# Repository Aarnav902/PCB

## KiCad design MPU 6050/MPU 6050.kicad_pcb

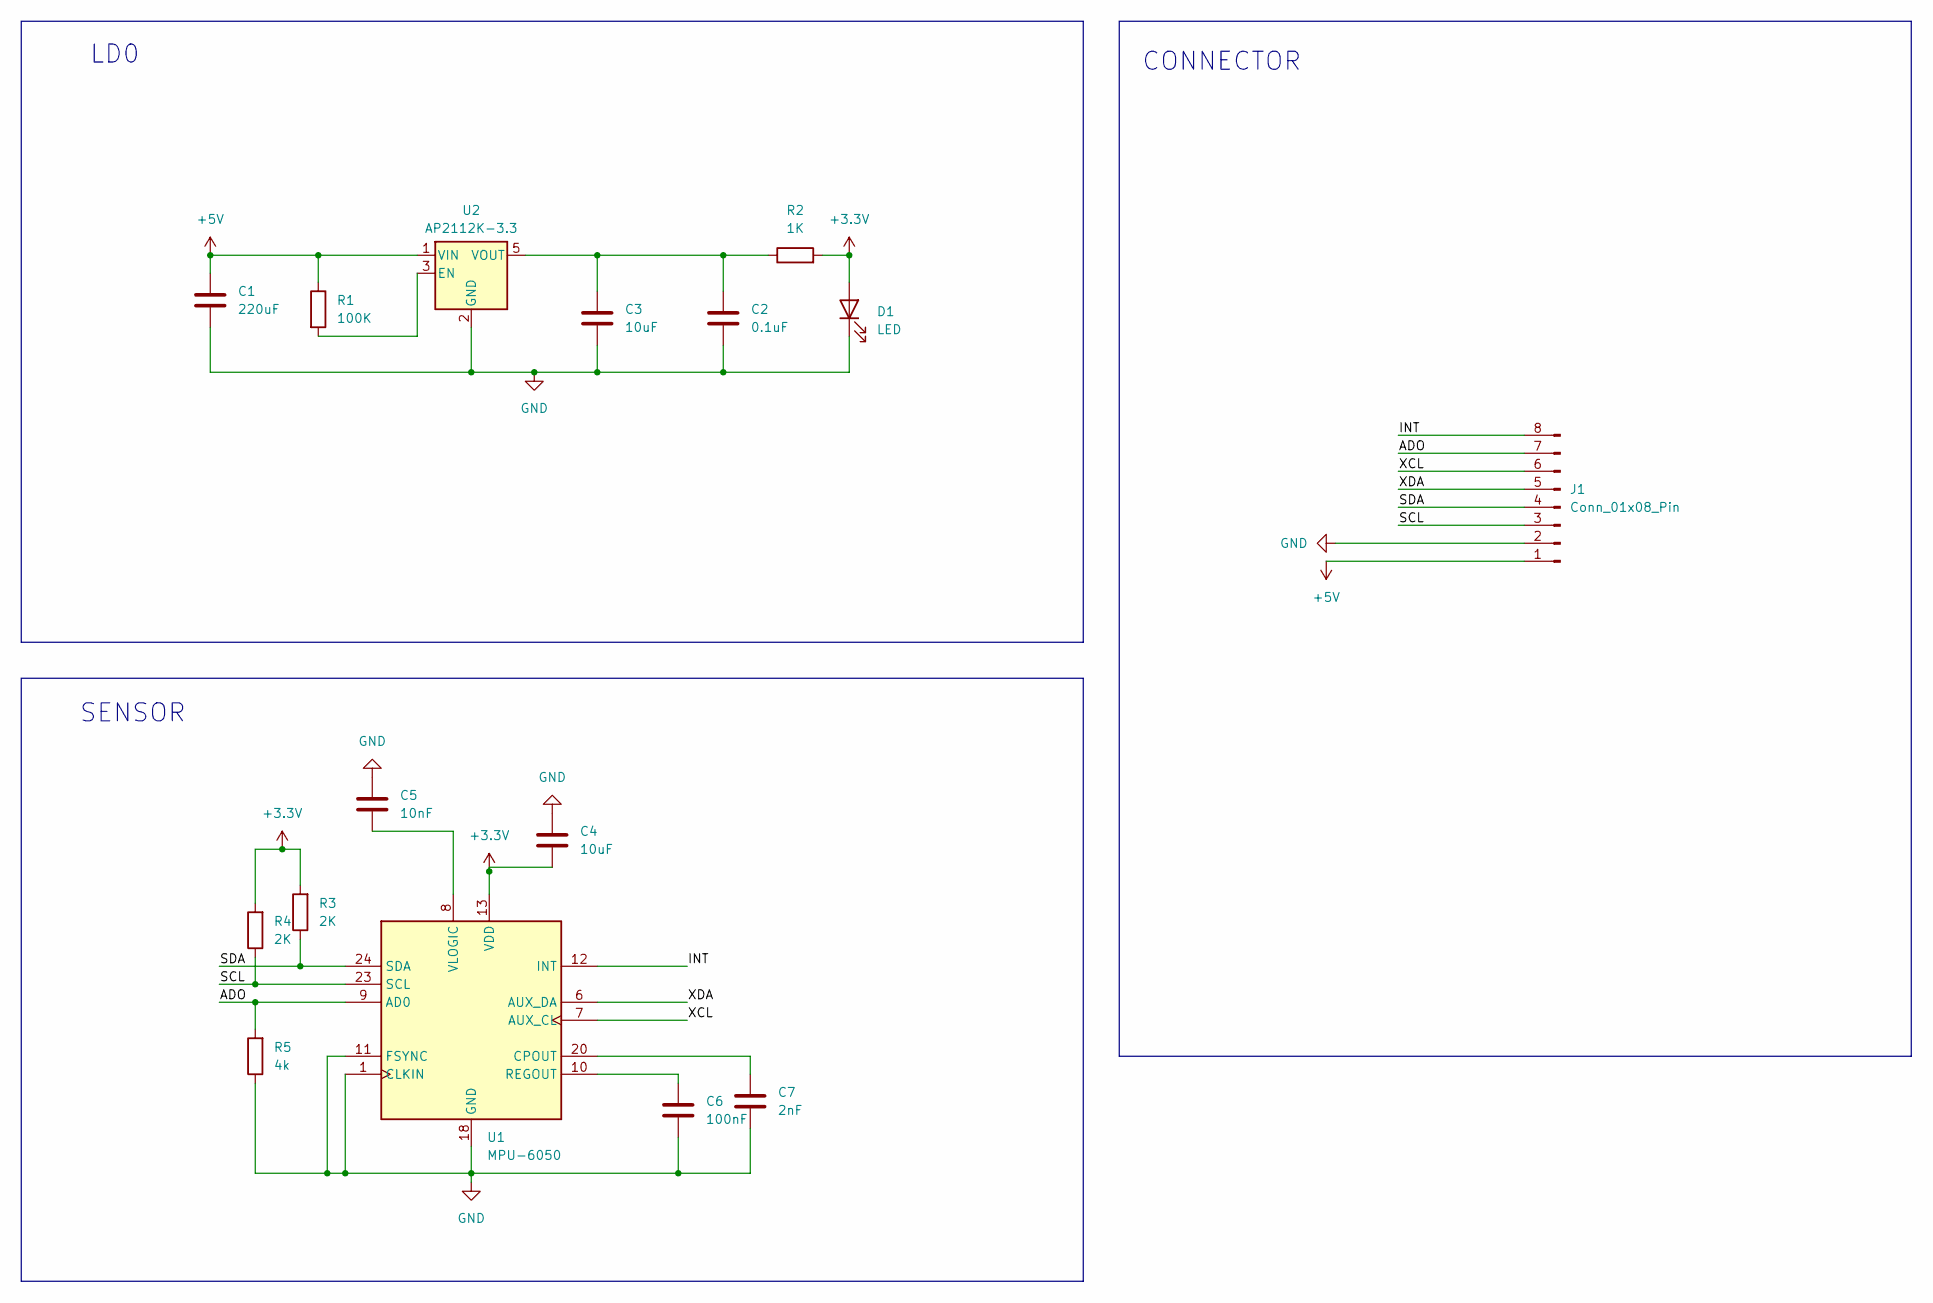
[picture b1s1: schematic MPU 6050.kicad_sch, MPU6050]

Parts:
C1: 220uF; C_0805_2012Metric
C2: 0.1uF; C_0603_1608Metric
C3, C4: 10uF; C_0805_2012Metric
C5: 10nF; C_0603_1608Metric
C6: 100nF; C_0603_1608Metric
C7: 2nF; C_0603_1608Metric
D1: LED; LED_0603_1608Metric
J1: Conn_01x08_Pin; PinHeader_1x08_P2.54mm_Vertical
R1: 100K; R_0603_1608Metric
R2: 1K; R_0603_1608Metric
R3, R4: 2K; R_0603_1608Metric
R5: 4k; R_0603_1608Metric
U1: MPU-6050; InvenSense_QFN-24_4x4mm_P0.5mm
U2: AP2112K-3.3; SOT-23-5

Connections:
+3.3V: C4.2, D1.2 (A), R2.2, R3.2, R4.2, U1.13 (VDD)
+5V: C1.1, J1.1, R1.1, U2.1 (VIN)
/ADO: J1.7, R5.2, U1.9 (AD0)
/INT: J1.8, U1.12 (INT)
/SCL: J1.3, R4.1, U1.23 (SCL)
/SDA: J1.4, R3.1, U1.24 (SDA)
/XCL: J1.6, U1.7 (AUX_CL)
/XDA: J1.5, U1.6 (AUX_DA)
GND: C1.2, C2.2, C3.2, C4.1, C5.1, C6.2, C7.2, D1.1 (K), J1.2, R5.1, U1.1 (CLKIN), U1.11 (FSYNC), U1.18 (GND), U2.2 (GND)
unnamed: C7.1, U1.20 (CPOUT)
unnamed: C6.1, U1.10 (REGOUT)
unnamed: C5.2, U1.8 (VLOGIC)
unnamed: R1.2, U2.3 (EN)
unnamed: C2.1, C3.1, R2.1, U2.5 (VOUT)

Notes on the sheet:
LD0
SENSOR
CONNECTOR

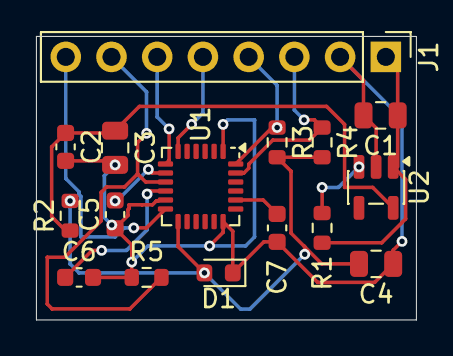
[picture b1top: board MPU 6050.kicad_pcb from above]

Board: 2 copper layers, 21.1 x 15.8 mm, 16 parts (0 on the bottom side), 14 nets.

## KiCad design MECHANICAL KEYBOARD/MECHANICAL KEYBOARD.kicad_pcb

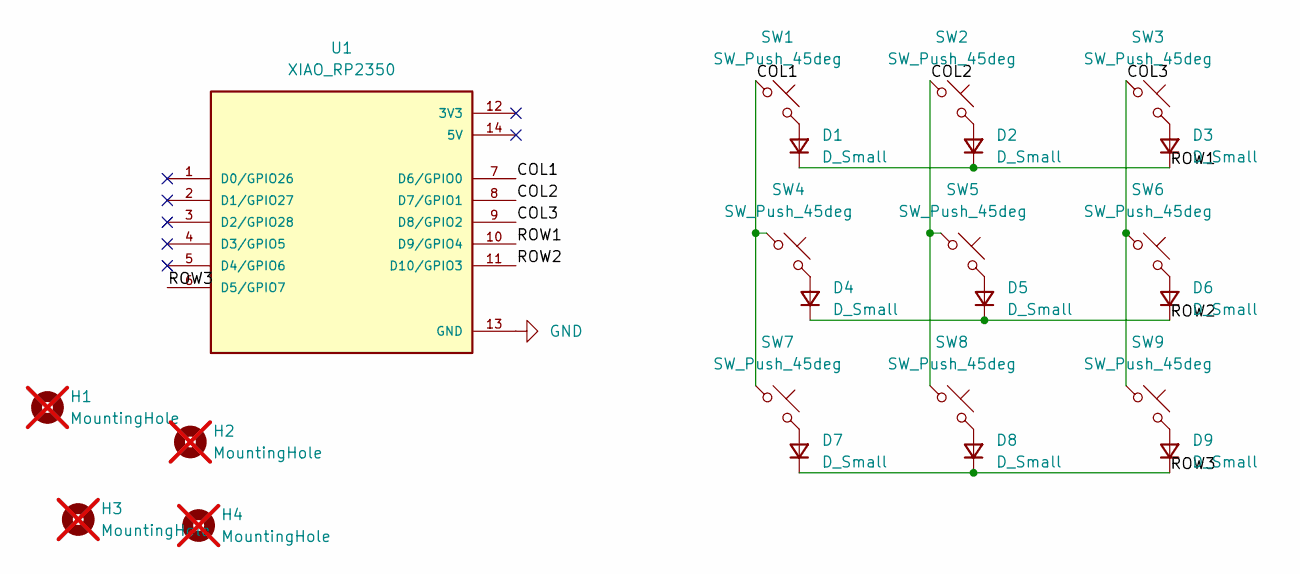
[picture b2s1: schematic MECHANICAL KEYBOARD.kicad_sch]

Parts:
D1, D2, D3, D4, D5, D6, D7, D8, D9: D_Small; D_SOD-123
H1, H2, H3, H4: MountingHole; MountingHole_3.2mm_M3; not fitted
SW1, SW2, SW3, SW4, SW5, SW6, SW7, SW8, SW9: SW_Push_45deg; SW_Cherry_MX_1.00u_PCB
U1: XIAO_RP2350; MODULE_XIAO_RP2350; PARTREV April 18th, 2026

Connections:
/COL1: SW1.1, SW4.1, SW7.1, U1.7 (D6/GPIO0)
/COL2: SW2.1, SW5.1, SW8.1, U1.8 (D7/GPIO1)
/COL3: SW3.1, SW6.1, SW9.1, U1.9 (D8/GPIO2)
/ROW1: D1.1 (K), D2.1 (K), D3.1 (K), U1.10 (D9/GPIO4)
/ROW2: D4.1 (K), D5.1 (K), D6.1 (K), U1.11 (D10/GPIO3)
/ROW3: D7.1 (K), D8.1 (K), D9.1 (K), U1.6 (D5/GPIO7)
GND: U1.13 (GND)
unnamed: D1.2 (A), SW1.2
unnamed: D2.2 (A), SW2.2
unnamed: D3.2 (A), SW3.2
unnamed: D4.2 (A), SW4.2
unnamed: D5.2 (A), SW5.2
unnamed: D6.2 (A), SW6.2
unnamed: D7.2 (A), SW7.2
unnamed: D8.2 (A), SW8.2
unnamed: D9.2 (A), SW9.2

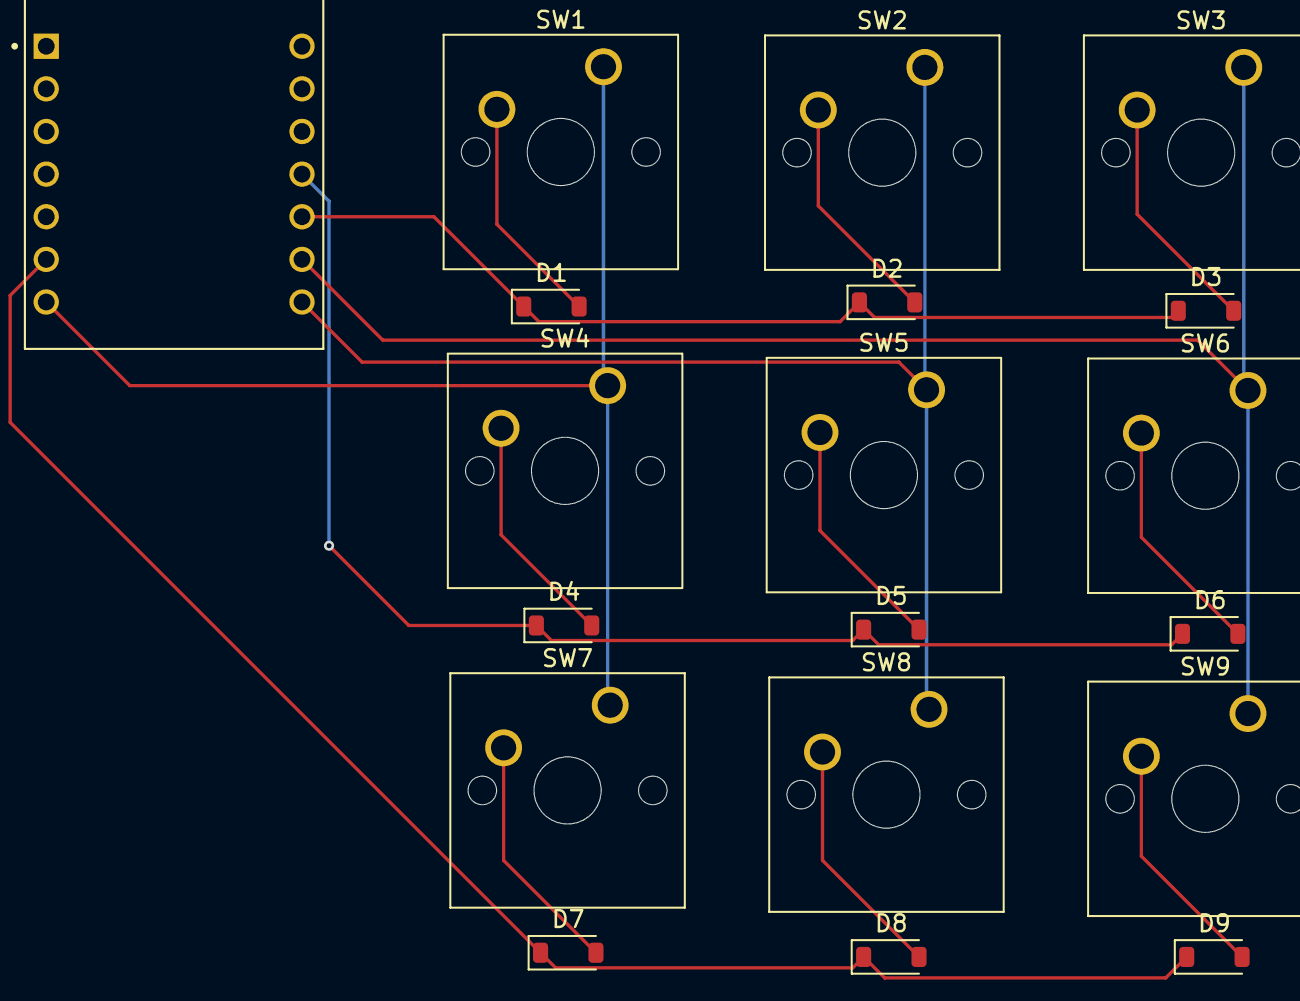
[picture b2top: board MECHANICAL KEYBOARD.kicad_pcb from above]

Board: 2 copper layers, 23 parts (0 on the bottom side), 15 nets.

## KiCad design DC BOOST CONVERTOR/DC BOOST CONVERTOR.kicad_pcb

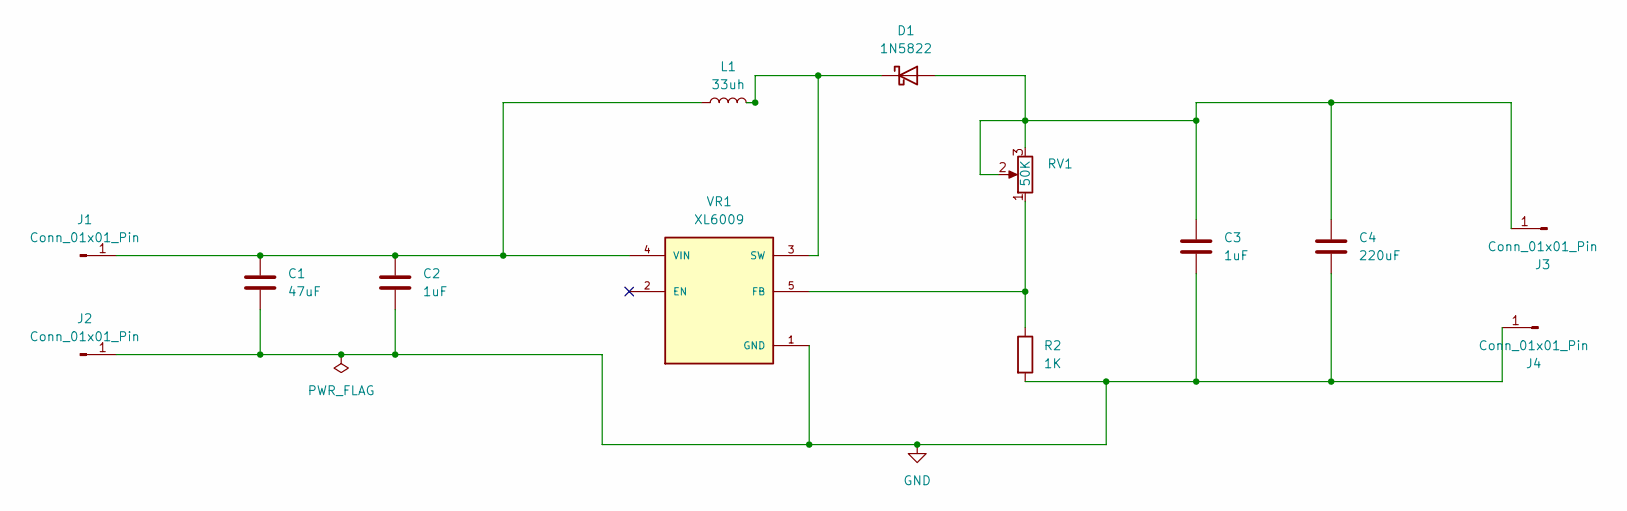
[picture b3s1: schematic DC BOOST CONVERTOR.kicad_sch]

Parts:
C1: 47uF; CP_Radial_D6.3mm_P2.50mm
C2, C3: 1uF; C_0805_2012Metric
C4: 220uF; CP_Radial_D8.0mm_P3.50mm
D1: 1N5822; D_DO-201AD_P15.24mm_Horizontal
J1, J2, J3, J4: Conn_01x01_Pin; Banana_Jack_1Pin
L1: 33uh; L_12x12mm_H8mm
R2: 1K; R_0805_2012Metric
RV1: 50K; Potentiometer_Bourns_3296W_Vertical
VR1: XL6009; DPAK170P1435X465-6N; PARTREV 1.1

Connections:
GND: C1.2, C2.2, C3.2, C4.2, J2.1 (Pin_1_1), J4.1 (Pin_1_1), R2.2, VR1.1 (GND)
unnamed: C3.1, C4.1, D1.2 (A), J3.1 (Pin_1_1), RV1.2, RV1.3
unnamed: D1.1 (K), L1.2, VR1.3 (SW), VR1.6 (SW)
unnamed: C1.1, C2.1, J1.1 (Pin_1_1), L1.1, VR1.4 (VIN)
unnamed: R2.1, RV1.1, VR1.5 (FB)

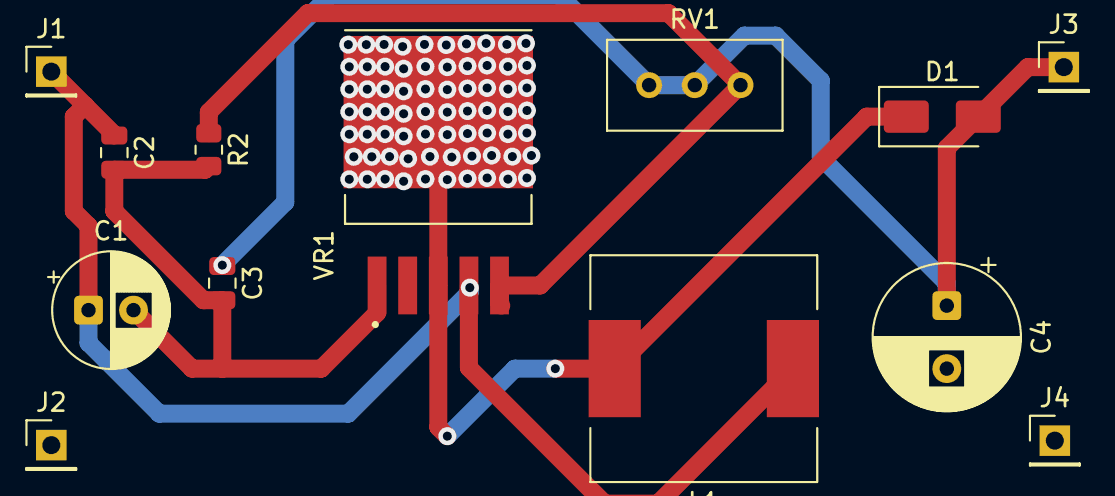
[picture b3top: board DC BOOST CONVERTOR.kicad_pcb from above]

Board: 2 copper layers, 13 parts (0 on the bottom side), 5 nets.

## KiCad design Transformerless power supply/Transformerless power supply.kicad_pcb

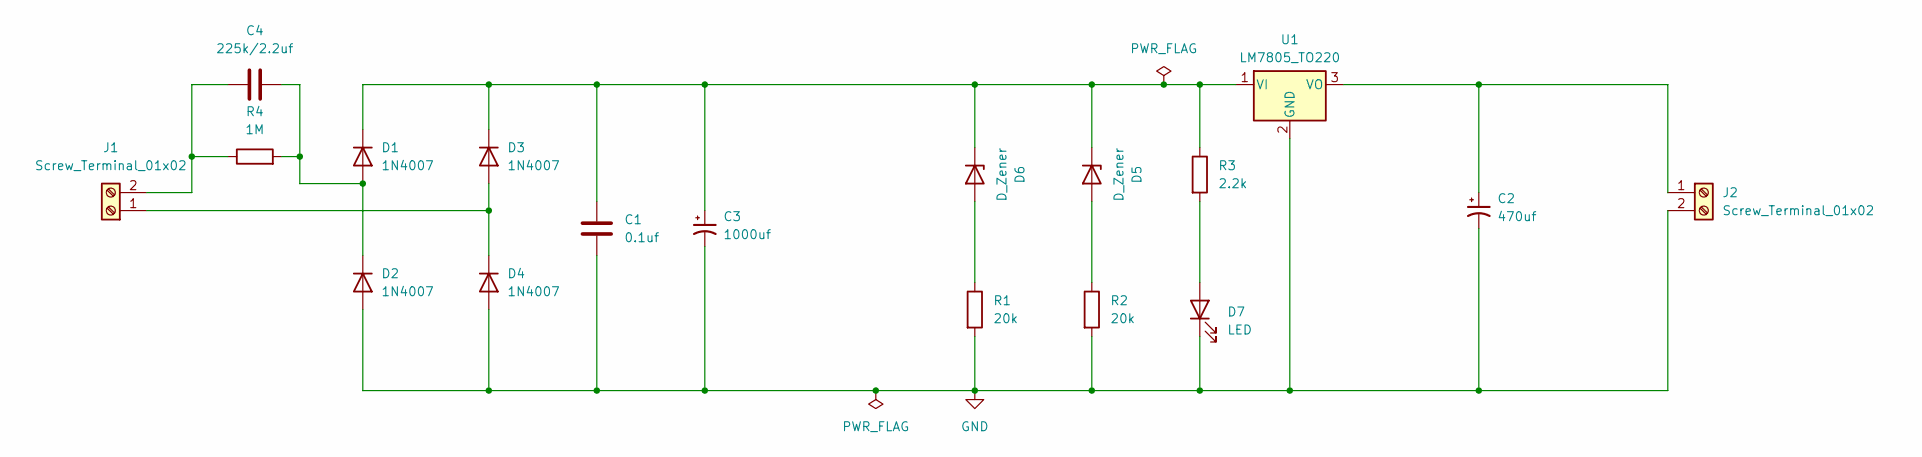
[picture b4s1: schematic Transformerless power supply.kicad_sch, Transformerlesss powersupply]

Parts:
C1: 0.1uf; C_Disc_D4.7mm_W2.5mm_P5.00mm
C2: 470uf; CP_Radial_D10.0mm_P3.80mm
C3: 1000uf; CP_Radial_D10.0mm_P5.00mm
C4: 225k/2.2uf; C_Rect_L18.0mm_W6.0mm_P15.00mm_FKS3_FKP3
D1, D2, D3, D4: 1N4007; D_DO-41_SOD81_P10.16mm_Horizontal
D5, D6: D_Zener; D_A-405_P7.62mm_Horizontal
D7: LED; LED_D5.0mm
J1, J2: Screw_Terminal_01x02; TerminalBlock_MaiXu_MX126-5.0-02P_1x02_P5.00mm
R1, R2: 20k; R_Axial_DIN0207_L6.3mm_D2.5mm_P7.62mm_Horizontal
R3: 2.2k; R_Axial_DIN0207_L6.3mm_D2.5mm_P7.62mm_Horizontal
R4: 1M; R_Axial_DIN0207_L6.3mm_D2.5mm_P7.62mm_Horizontal
U1: LM7805_TO220; TO-220-3_Vertical

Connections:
GND: C1.2, C2.2, C3.2, D2.2 (A), D4.2 (A), D7.1 (K), J2.2, R1.2, R2.2, U1.2 (GND)
unnamed: C4.2, D1.2 (A), D2.1 (K), R4.2
unnamed: C1.1, C3.1, D1.1 (K), D3.1 (K), D5.1 (K), D6.1 (K), R3.1, U1.1 (VI)
unnamed: D3.2 (A), D4.1 (K), J1.1
unnamed: D5.2 (A), R2.1
unnamed: D6.2 (A), R1.1
unnamed: D7.2 (A), R3.2
unnamed: C4.1, J1.2, R4.1
unnamed: C2.1, J2.1, U1.3 (VO)

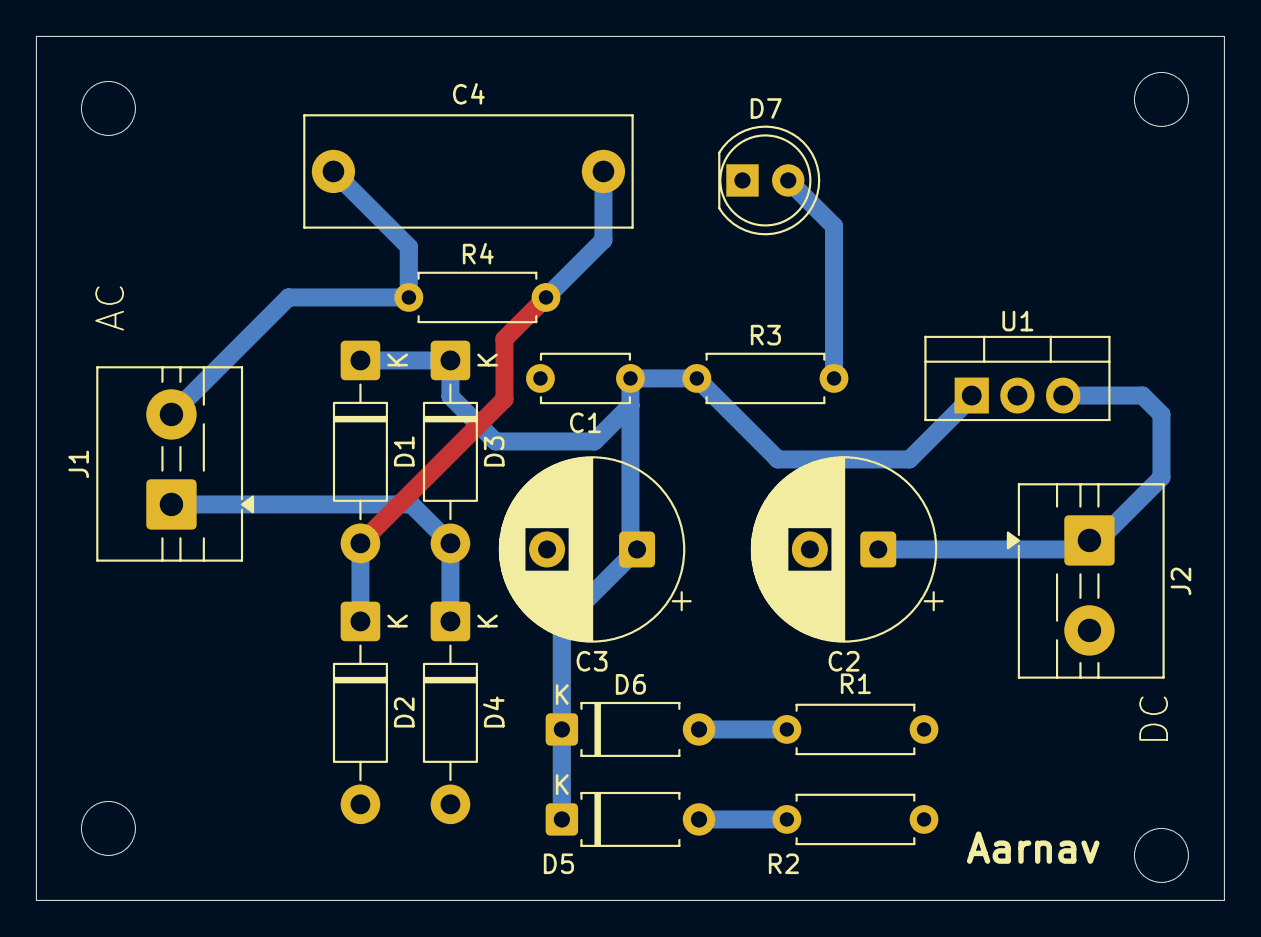
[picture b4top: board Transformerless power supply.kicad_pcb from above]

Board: 2 copper layers, 66.0 x 48.0 mm, 18 parts (0 on the bottom side), 9 nets.

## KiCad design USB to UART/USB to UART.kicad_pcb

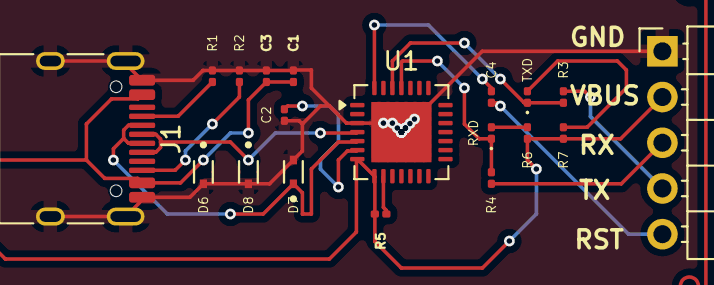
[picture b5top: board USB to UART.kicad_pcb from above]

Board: 2 copper layers, 19 parts (0 on the bottom side), 16 nets.

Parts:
C1, C2, C3, C4: 100nF; C_0201_0603Metric
D6, D7, D8: LESD5D5.0CT1G; TVS_LESD5D5.0CT1G
J1: USB_C_Receptacle_USB2.0_16P; USB_C_Receptacle_HRO_TYPE-C-31-M-12
J2: Conn_01x05_Pin; PinHeader_1x05_P2.54mm_Horizontal
R1, R2: 5.1k; R_0201_0603Metric
R3, R4, R6, R7: 1K; R_0201_0603Metric
R5: 10K; R_0201_0603Metric
RXD: LED; LED_0201_0603Metric
TXD: LED; LED_0201_0603Metric
U1: CP2102N-Axx-xQFN28; QFN-28-1EP_5x5mm_P0.5mm_EP3.35x3.35mm

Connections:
/D+: D8.1, J1.A6 (D+), J1.B6 (D+), U1.4 (D+)
/D-: D7.1, J1.A7 (D-), J1.B7 (D-), U1.5 (D-)
/RST: C4.2, J2.5
/RX: J2.3, R4.1
/TX: J2.4, R3.1
/VBUS: C1.2, C3.2, D6.1, J1.A4 (VBUS), J1.A9 (VBUS), J1.B4 (VBUS), J1.B9 (VBUS), J2.2, R5.1, R6.1, R7.1, U1.7 (VREGIN), U1.8 (VBUS)
GND: C1.1, C2.1, C3.1, D6.2, D7.2, D8.2, J1.A1 (GND), J1.A12 (GND), J1.B1 (GND), J1.B12 (GND), J1.SH (SHIELD), J2.1, R1.2, R2.2, U1.3 (GND), U1.29 (GND)
unnamed: R7.2, TXD.2 (A)
unnamed: R3.2, TXD.1 (K), U1.26 (TXD)
unnamed: R6.2, RXD.2 (A)
unnamed: R4.2, RXD.1 (K), U1.25 (RXD)
unnamed: J1.A5 (CC1), R1.1
unnamed: J1.B5 (CC2), R2.1
unnamed: C2.2, U1.6 (VDD)
unnamed: C4.1, U1.28 (~DTR)
unnamed: R5.2, U1.9 (~RST)

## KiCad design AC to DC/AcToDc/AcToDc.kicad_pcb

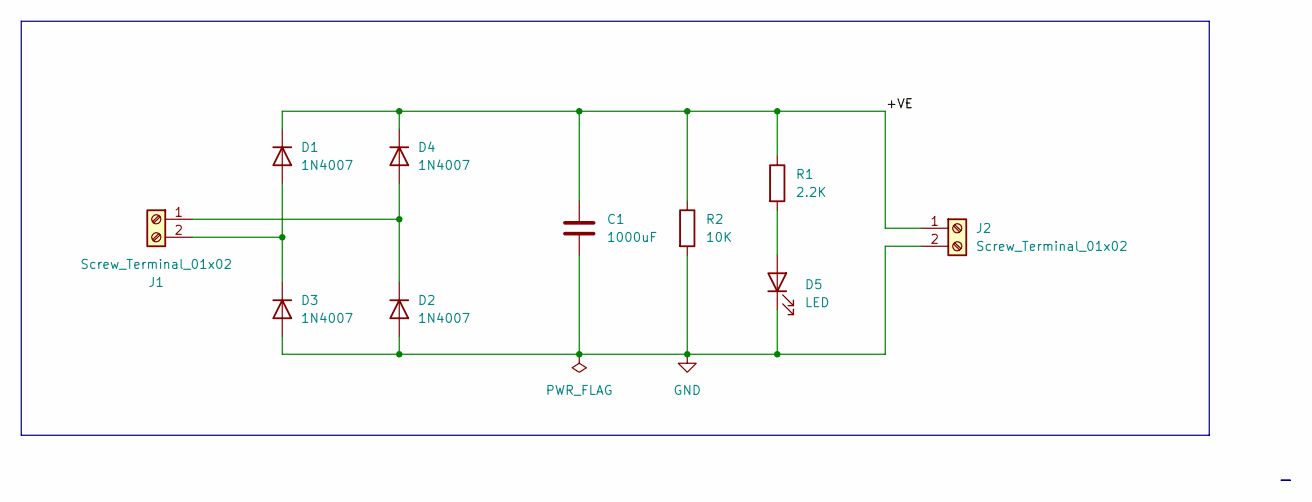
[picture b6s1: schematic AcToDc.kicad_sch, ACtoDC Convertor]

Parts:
C1: 1000uF; CP_Radial_D8.0mm_P3.50mm
D1, D2, D3, D4: 1N4007; D_DO-41_SOD81_P10.16mm_Horizontal
D5: LED; LED_D5.0mm
J1, J2: Screw_Terminal_01x02; TerminalBlock_MaiXu_MX126-5.0-02P_1x02_P5.00mm
R1: 2.2K; R_Axial_DIN0204_L3.6mm_D1.6mm_P7.62mm_Horizontal
R2: 10K; R_Axial_DIN0204_L3.6mm_D1.6mm_P7.62mm_Horizontal

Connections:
/+VE: C1.1, D1.1 (K), D4.1 (K), J2.1, R1.1, R2.1
GND: C1.2, D2.2 (A), D3.2 (A), D5.1 (K), J2.2, R2.2
unnamed: D1.2 (A), D3.1 (K), J1.2
unnamed: D2.1 (K), D4.2 (A), J1.1
unnamed: D5.2 (A), R1.2

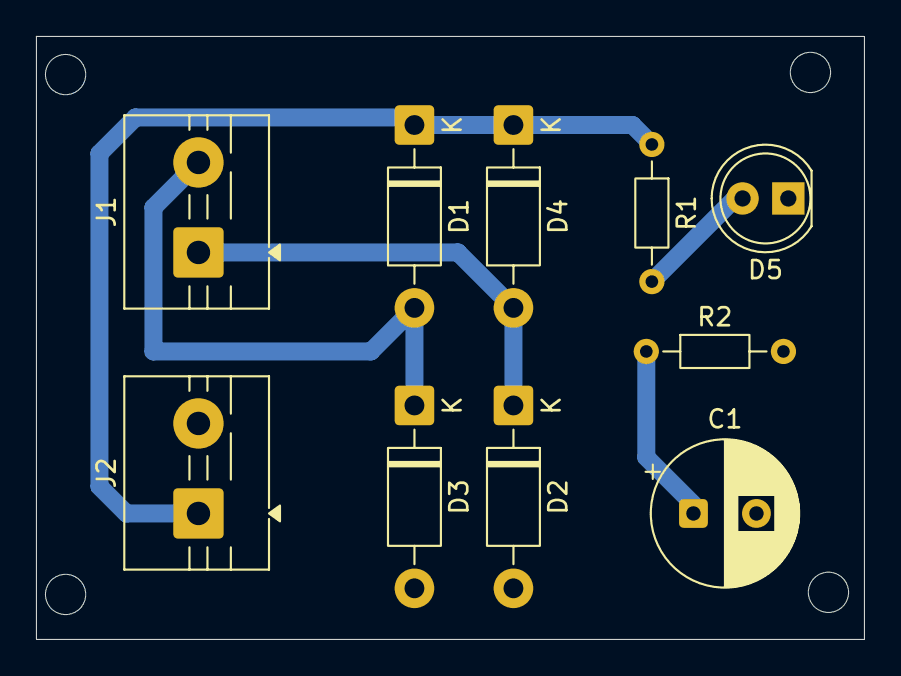
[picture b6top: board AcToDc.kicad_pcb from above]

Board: 2 copper layers, 46.0 x 33.5 mm, 10 parts (0 on the bottom side), 5 nets.

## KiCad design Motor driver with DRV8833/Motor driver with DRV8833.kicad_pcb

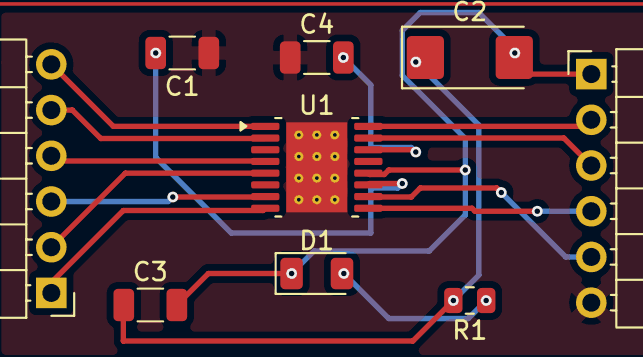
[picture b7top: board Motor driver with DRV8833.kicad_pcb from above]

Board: 2 copper layers, 9 parts (0 on the bottom side), 16 nets.

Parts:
C1, C3: 0.1uF; C_1206_3216Metric
C2: 10uF; CP_EIA-6032-20_AVX-F
C4: 2.2uF; C_1206_3216Metric
D1: LED; LED_1206_3216Metric
J1, J2: Conn_01x06_Pin; PinHeader_1x06_P2.54mm_Horizontal
R1: 4.7K; R_0805_2012Metric
U1: DRV8833PWP; HTSSOP-16-1EP_4.4x5mm_P0.65mm_EP3.4x5mm_Mask2.46x2.31mm_The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

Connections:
/AIN1: J1.2, U1.16 (AIN1)
/AIN2: J1.3, U1.15 (AIN2)
/AOUT1: J2.5, U1.2 (AOUT1)
/AOUT2: J2.4, U1.4 (AOUT2)
/BIN1: J1.4, U1.9 (BIN1)
/BIN2: J1.5, U1.10 (BIN2)
/BOUT1: J2.3, U1.7 (BOUT1)
/BOUT2: J2.2, U1.5 (BOUT2)
/FAULT: J2.1, U1.8 (~FAULT)
/SLEEP: J2.6, U1.1 (~SLEEP)
/VCC: C2.2, C3.2, D1.1 (K), J1.1, U1.12 (VM)
GND: C1.1, C4.1, J1.6, U1.3 (AISEN), U1.6 (BISEN), U1.13 (GND), U1.17 (GND)
unnamed: C2.1, C3.1, R1.2
unnamed: D1.2 (A), R1.1
unnamed: C1.2, U1.11 (VCP)
unnamed: C4.2, U1.14 (VINT)
